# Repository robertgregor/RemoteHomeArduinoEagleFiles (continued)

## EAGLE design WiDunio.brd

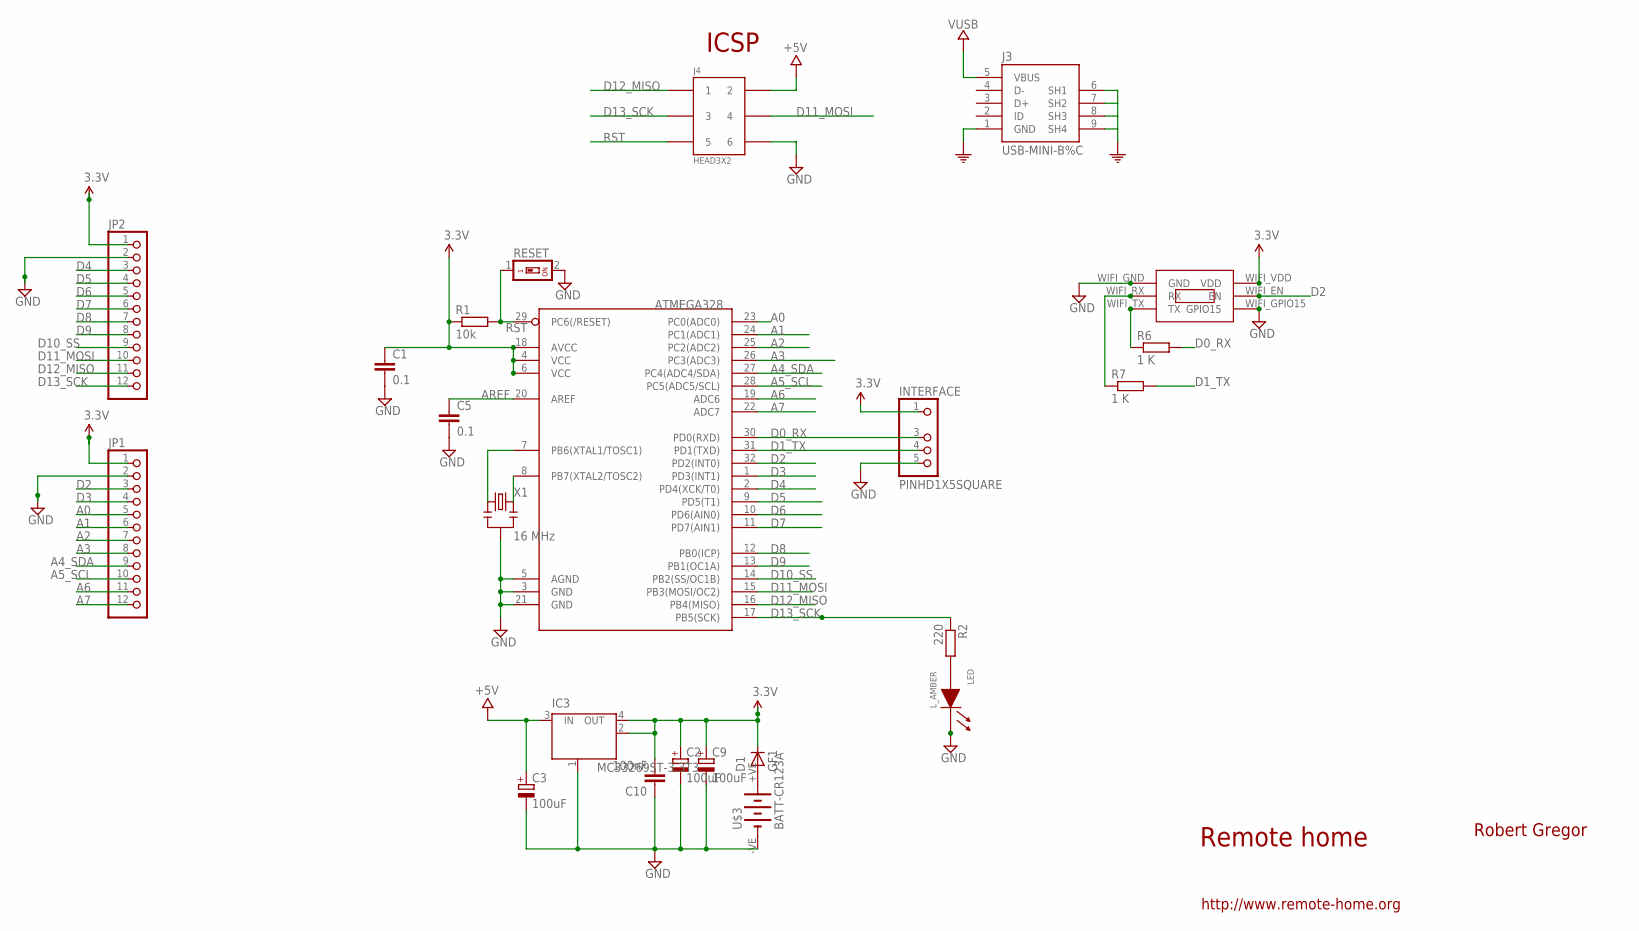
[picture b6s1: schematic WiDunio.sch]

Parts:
ATMEGA328: ATMega-328; TQFP32-08
C1, C5: 0.1; C2012
C2, C3, C9: 100uF; SMC_B
C10: 100nF; C2012
D1: GF1; SMA-DO214AC
IC3: MC33269ST-3.3T3; SOT223
INTERFACE: PINHD1X5SQUARE; PINHD1X05-SQUARE
J3: USB-MINI-B%C; USB-MINI-B_2
J4: HEAD3X2
JP1, JP2: PINHD-1X12; 1X12
LED: L_AMBER; LED0805
R1: 10k; R2012
R2: 220; M2012
R6, R7: 1 K; M2012
RESET: SWS001; SMS-001
U$3: BATT-CR123A; KEYSTONE-2/3A
U$5: ESP03
X1: 16 MHz; RESONATOR-SMD

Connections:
5V: C3.+, IC3.3 (IN), J3.5 (VBUS), J4.2
A0: ATMEGA328.23 (PC0(ADC0)), JP1.5
A1: ATMEGA328.24 (PC1(ADC1)), JP1.6
A2: ATMEGA328.25 (PC2(ADC2)), JP1.7
A3: ATMEGA328.26 (PC3(ADC3)), JP1.8
A4_SDA: ATMEGA328.27 (PC4(ADC4/SDA)), JP1.9
A5_SCL: ATMEGA328.28 (PC5(ADC5/SCL)), JP1.10
A6: ATMEGA328.19 (ADC6), JP1.11
A7: ATMEGA328.22 (ADC7), JP1.12
AREF: ATMEGA328.20 (AREF), C5.1
D0_RX: ATMEGA328.30 (PD0(RXD)), INTERFACE.3, R6.2
D1_TX: ATMEGA328.31 (PD1(TXD)), INTERFACE.4, R7.2
D2: ATMEGA328.32 (PD2(INT0)), JP1.3, U$5.WIFI_EN (EN)
D3: ATMEGA328.1 (PD3(INT1)), JP1.4
D4: ATMEGA328.2 (PD4(XCK/T0)), JP2.3
D5: ATMEGA328.9 (PD5(T1)), JP2.4
D6: ATMEGA328.10 (PD6(AIN0)), JP2.5
D7: ATMEGA328.11 (PD7(AIN1)), JP2.6
D8: ATMEGA328.12 (PB0(ICP)), JP2.7
D9: ATMEGA328.13 (PB1(OC1A)), JP2.8
D10_SS: ATMEGA328.14 (PB2(SS/OC1B)), JP2.9
D11_MOSI: ATMEGA328.15 (PB3(MOSI/OC2)), J4.4, JP2.10
D12_MISO: ATMEGA328.16 (PB4(MISO)), J4.1, JP2.11
D13_SCK: ATMEGA328.17 (PB5(SCK)), J4.3, JP2.12, R2.1
GND: ATMEGA328.3 (GND), ATMEGA328.5 (AGND), ATMEGA328.21 (GND), C1.2, C2.-, C3.-, C5.2, C9.-, C10.1, IC3.1 (GND/ADJ), INTERFACE.5, J3.1 (GND), J3.6 (SH1), J3.7 (SH2), J3.8 (SH3), J3.9 (SH4), J4.6, JP1.2, JP2.2, LED.1 (CA), RESET.2, U$3.-VE (-), U$5.WIFI_GND (GND), U$5.WIFI_GPIO15 (GPIO15), X1.2
unnamed: ATMEGA328.7 (PB6(XTAL1/TOSC1)), X1.1
unnamed: D1.A, U$3.+VE (+)
unnamed: LED.2 (AN), R2.2
unnamed: R6.1, U$5.WIFI_TX (TX)
unnamed: R7.1, U$5.WIFI_RX (RX)
unnamed: ATMEGA328.8 (PB7(XTAL2/TOSC2)), X1.3
RST: ATMEGA328.29 (PC6(/RESET)), J4.5, R1.2, RESET.1
VCC: ATMEGA328.4 (VCC), ATMEGA328.6 (VCC), ATMEGA328.18 (AVCC), C1.1, C2.+, C9.+, C10.2, D1.K (C), IC3.2 (OUT), IC3.4 (OUT), INTERFACE.1, JP1.1, JP2.1, R1.1, U$5.WIFI_VDD (VDD)

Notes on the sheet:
Remote home
Robert Gregor
http://www.remote-home.org
ICSP

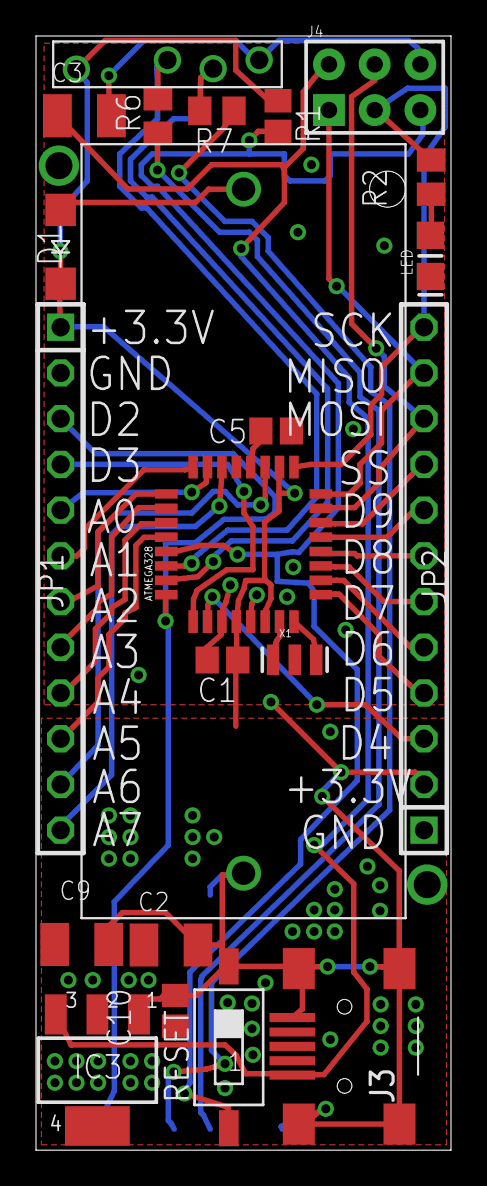
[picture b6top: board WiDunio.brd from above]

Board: 2 copper layers, 23.1 x 61.9 mm, 23 parts (1 on the bottom side), 33 nets.

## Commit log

2014-03-16 Initial version
2014-05-01 Fixed bugs
2014-12-24 aaa
    aaa
2015-03-09 bugfix
